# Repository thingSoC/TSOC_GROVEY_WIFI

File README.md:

# TSOC-GROVEY_WIFI

**TSOC-GROVEY_WIFI** is a Wi-Fi Embedded Module, **thingSoC Reference Design.** 

**thingSoC Reference Designs** are example thingSoC implementations that implement
various reference and testing circuits for demonstrating the use of the thingSoC libraries.
These reference designs are complete designs and can also serve as starting templates for users to customize.

**TSOC-GROVEY_WIFI** includes an ESP8266-07/12E format Wi-Fi module, in a thingSoC compatible pinout.

---------------------------------------

[  
*TSOC-GROVEY_WIFI*](https://github.com/thingSoC/thingSoC/tree/master/examples/eagle6/TSOC-GROVEY_WIFI)

* [Supported by the Arduino IDE](https://www.arduino.cc/) 
* Wi-Fi and OTA (Over the Air) Program Upgrade/Download
* thingSoC Compliant Module
* [Mikrobus Compatible Module](http://www.mikroe.com/mikrobus/) 
* ESP8266 Wi-Fi Module 802.11 b/g/n
* +19.5dBm output power in 802.11b mode
* Wi-Fi Direct (P2P), soft-AP
* Integrated TCP/IP protocol stack
* Internal Antenna and U.FL external Antenna Support

---------------------------------------

## Documentation Index <a name="documentation_index"/>

For ESP8266 Documentation (esp. toolchain info) see [NurdSpace](https://nurdspace.nl/ESP8266)

[thingSoC Organization Website](http://thingSoC.github.io)

[thingSoC FAQ - Frequently Asked Questions](http://thingsoc.github.io/support/faq.html)

---------------------------------------

[  
*thingSoC*](http://thingsoc.github.io)

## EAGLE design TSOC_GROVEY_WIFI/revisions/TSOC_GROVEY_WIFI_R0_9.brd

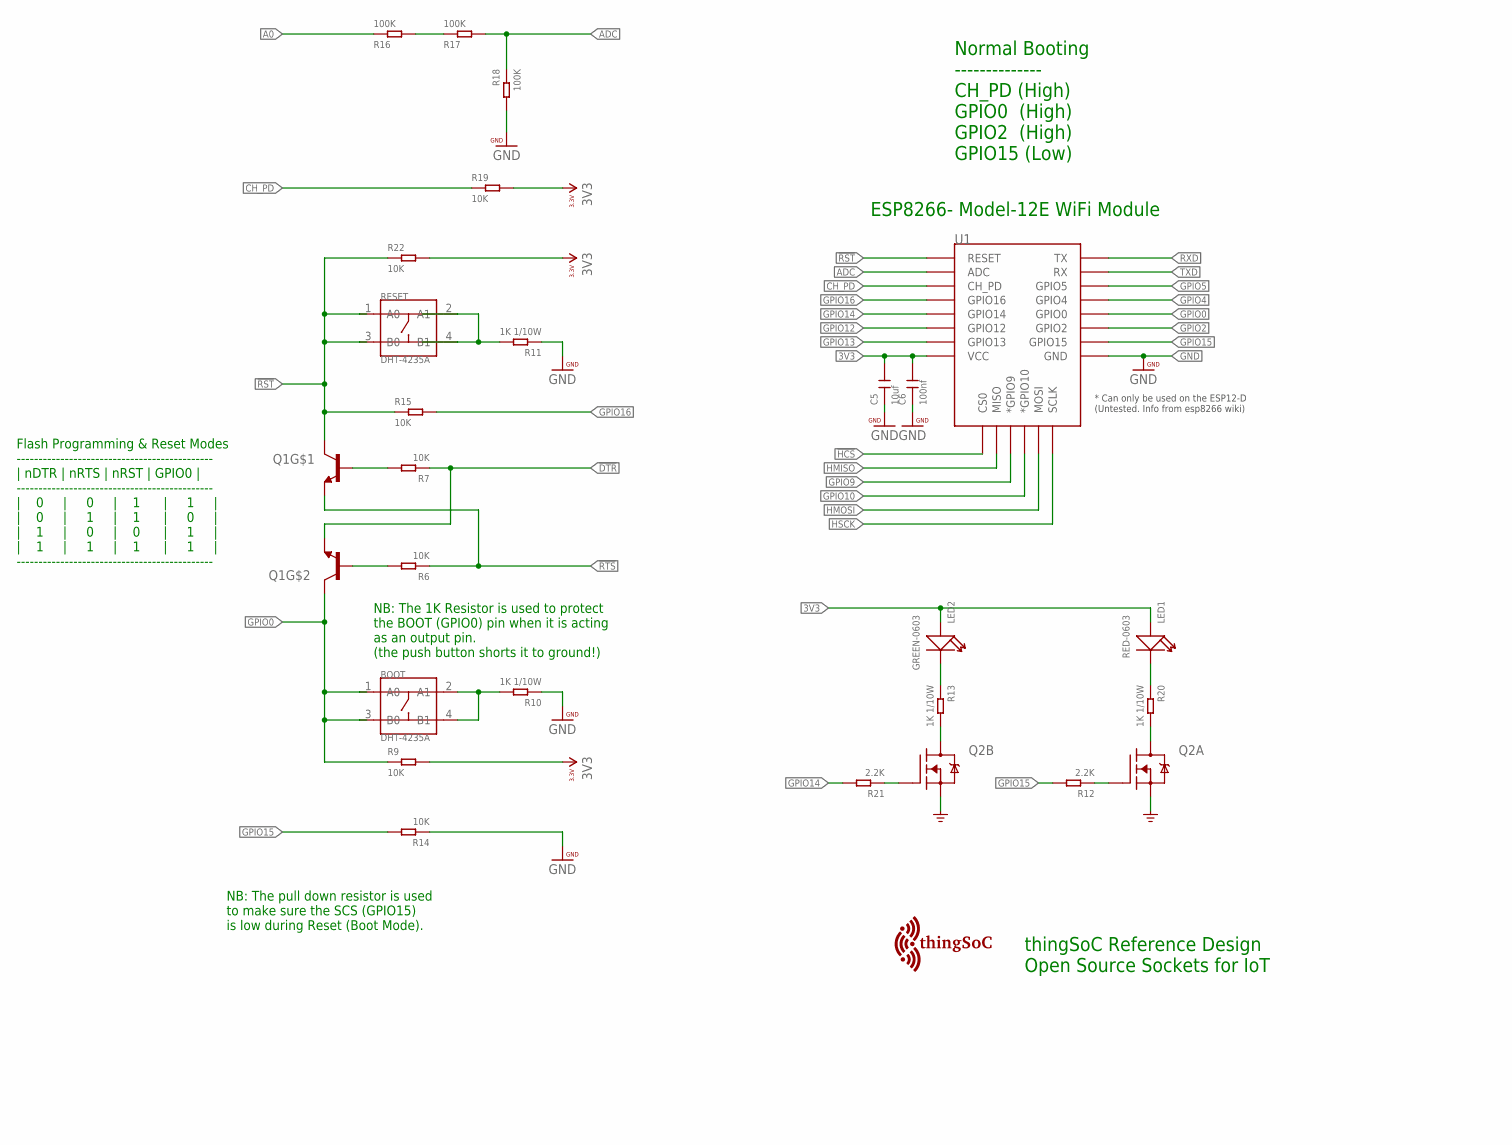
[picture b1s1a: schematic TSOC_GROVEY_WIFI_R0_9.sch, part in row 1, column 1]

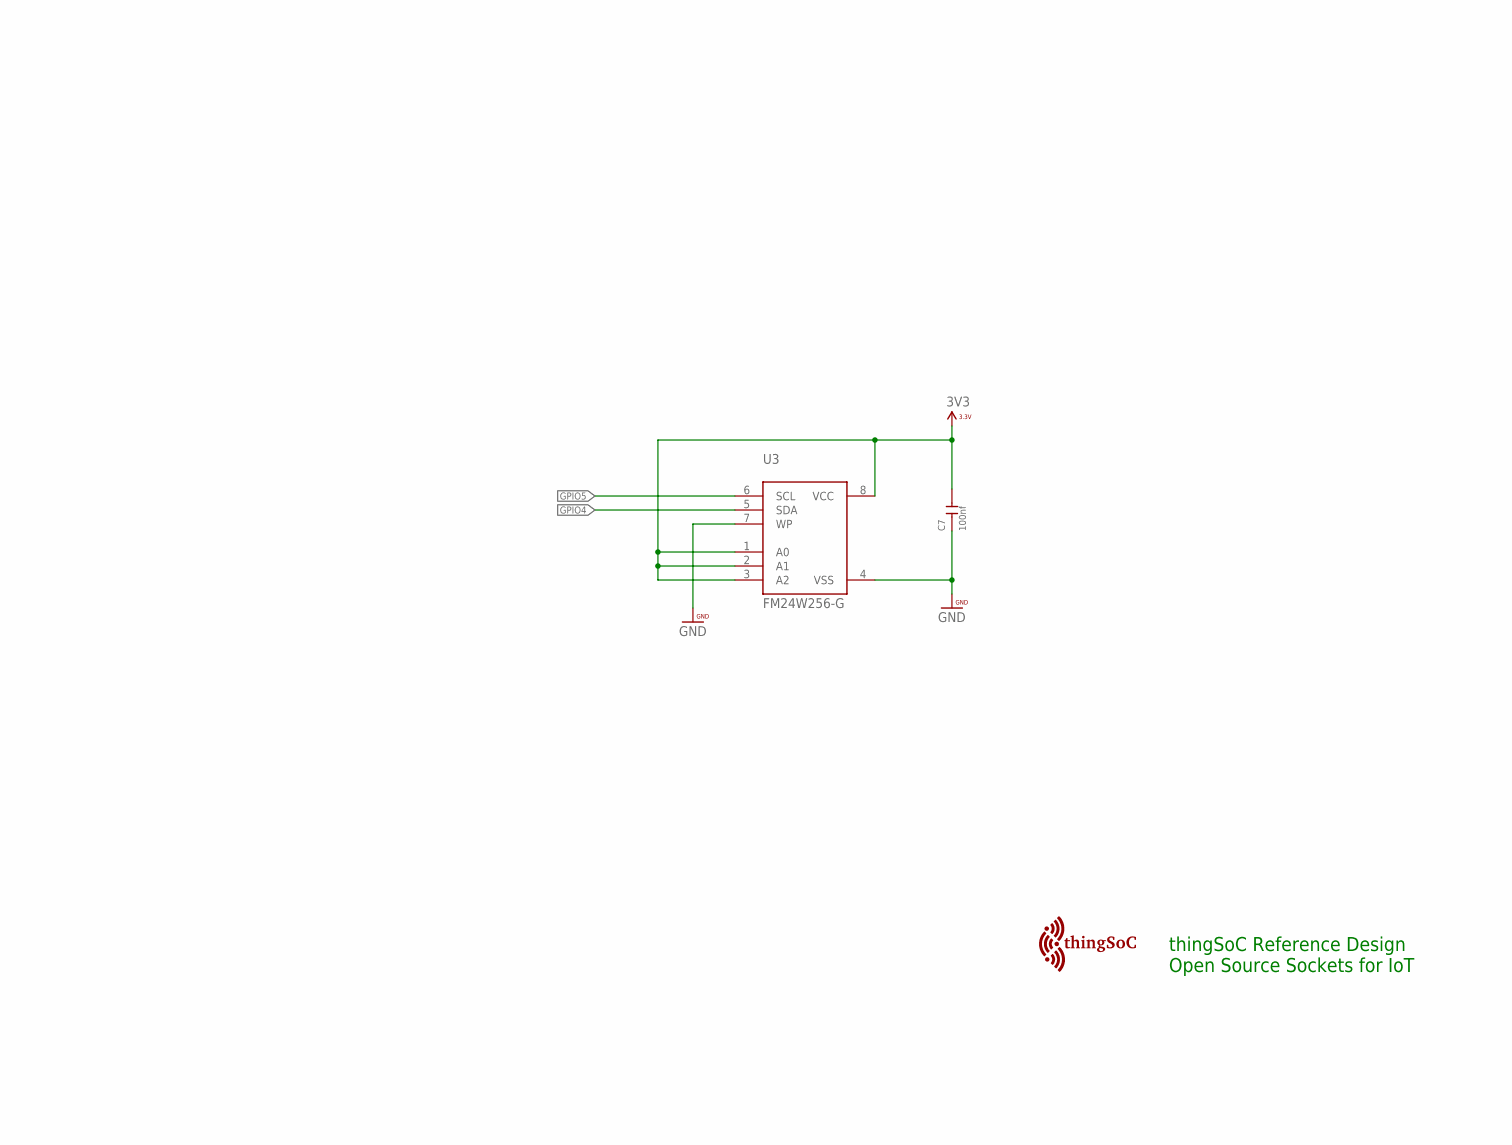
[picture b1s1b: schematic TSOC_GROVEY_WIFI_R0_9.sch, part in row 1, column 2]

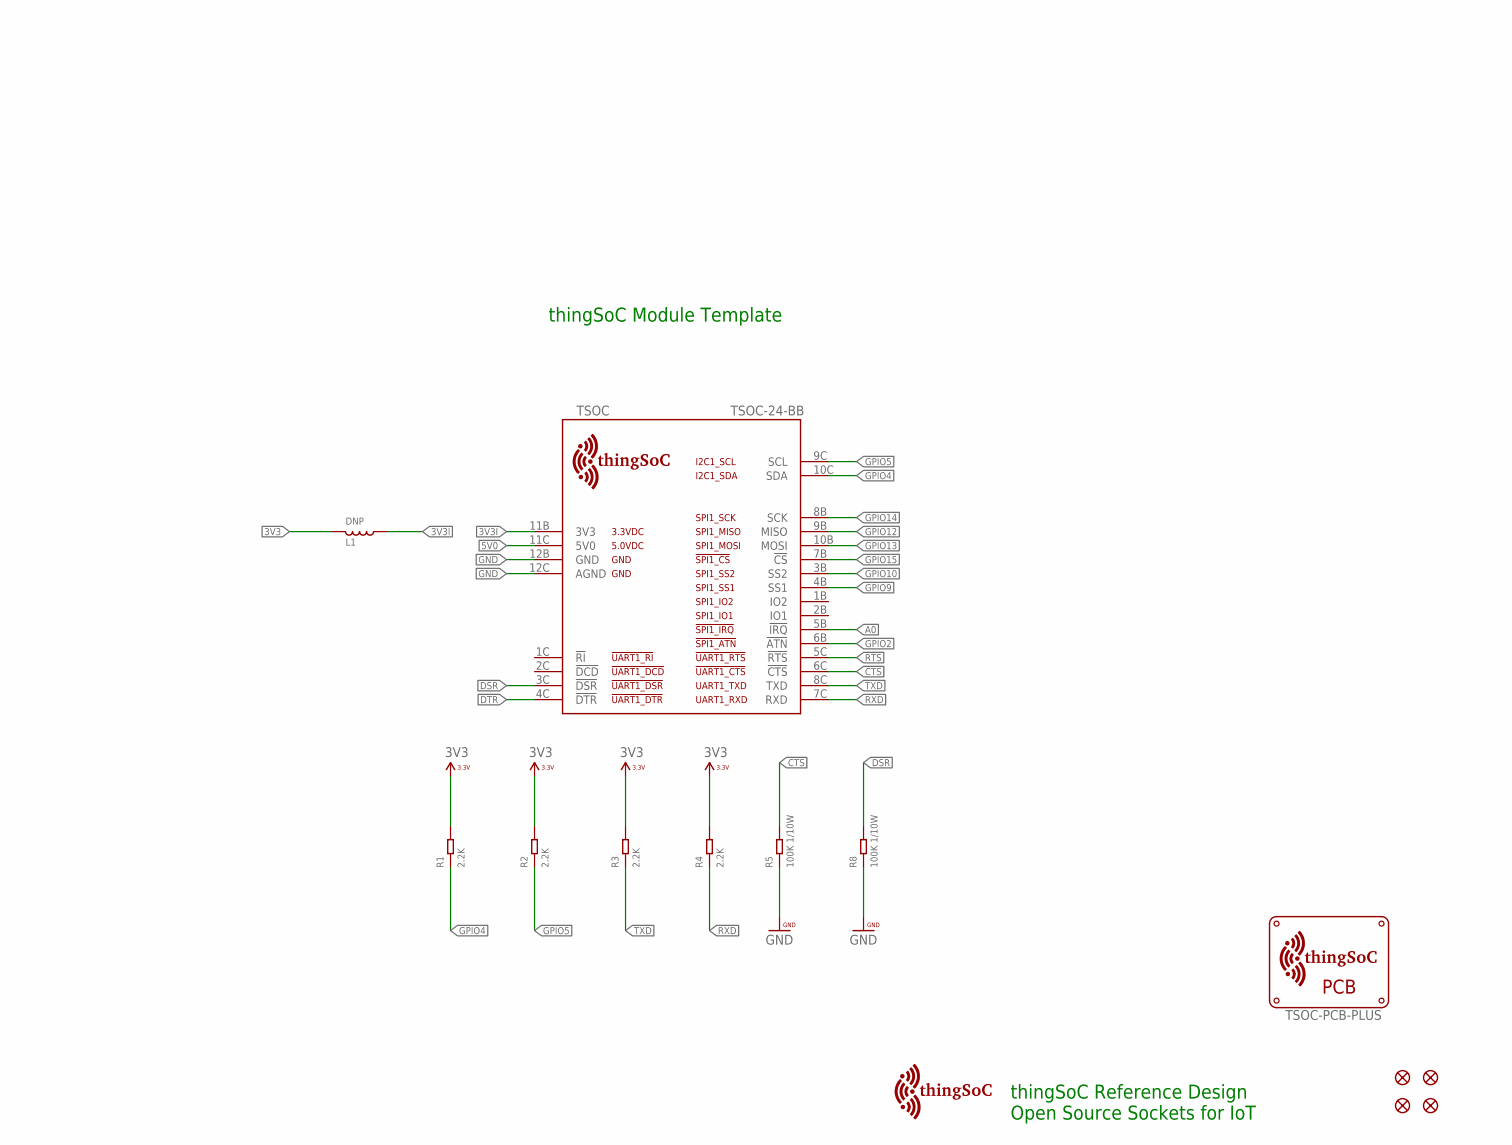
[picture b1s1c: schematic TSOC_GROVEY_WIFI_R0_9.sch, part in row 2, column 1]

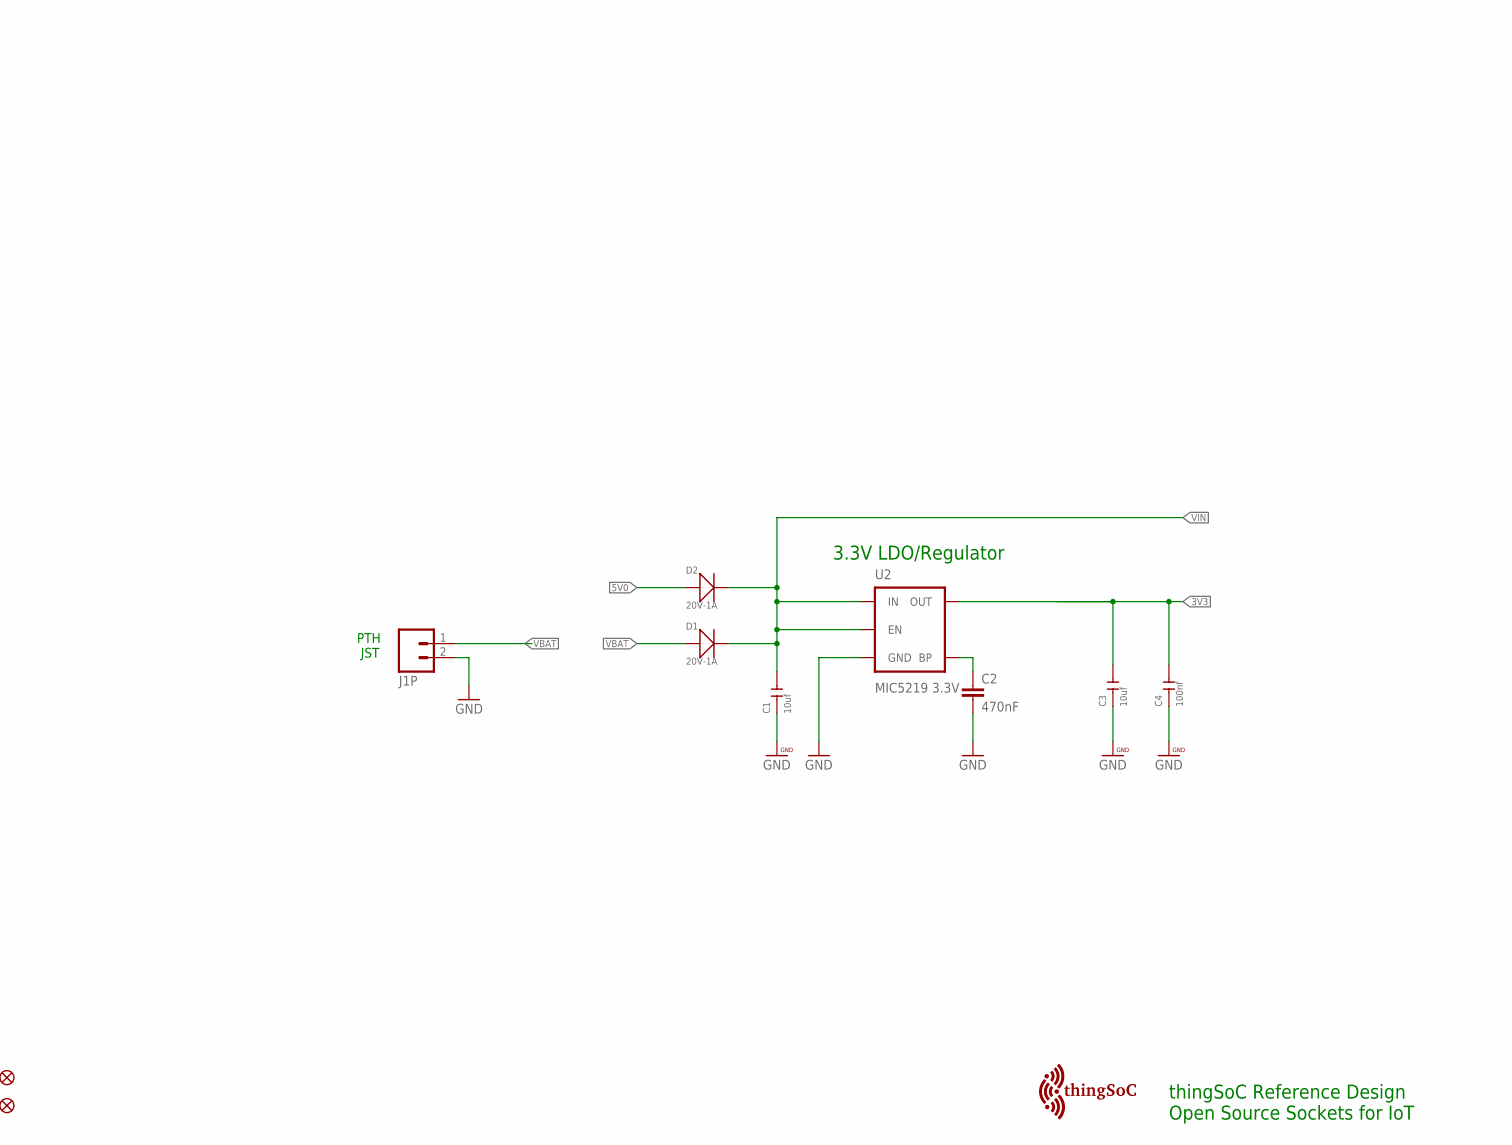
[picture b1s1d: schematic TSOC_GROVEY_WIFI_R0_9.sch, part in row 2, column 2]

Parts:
BOOT: DHT-4235A; SW4-SMD-4.2X3.2X2.5MM
C1, C3, C5: 10uf; C1206
C2: 470nF; 0402-CAP
C4, C6, C7: 100nf; C0603
D1, D2: 20V-1A; SOD-123
FID1, FID2, FID3, FID4: FIDUCIALUFIDUCIAL; MICRO-FIDUCIAL
J1P: M02-JST-2-PTH-NO_SILK; JST-2-PTH-NS
L1: DNP; L0603
LED1: RED-0603; LED-0603
LED2: GREEN-0603; LED-0603
PCB: TSOC-PCB-PLUS; TSOC-BB-BRD-PLUS-DIM
Q1: MMBT2222A; SOT363
Q2: FDG1024NZ; SOT95P280X110-6N
R1, R2, R3, R4, R12, R21: 2.2K; R0603
R5, R8: 100K 1/10W; R0603
R6, R7, R9, R14, R15, R19, R22: 10K; R0603
R10, R11, R13, R20: 1K 1/10W; R0603
R16, R17, R18: 100K; R0603
RESET: DHT-4235A; SW4-SMD-4.2X3.2X2.5MM
TSOC: TSOC-24-BB; TSOC-BB-S24
U1: ESP12ESMD; ESP12E-SMD
U2: MIC5219 3.3V; SOT23-5
U3: FM24W256-G; SO08
U$22, U$23, U$26, U$28: TSOC-LOGO-MED

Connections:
3V3: C3.2, C4.2, C5.2, C6.2, C7.2, L1.1, LED1.+, LED2.+, R1.2, R2.2, R3.2, R4.2, R9.2, R19.2, R22.2, U1.VCC, U2.5 (OUT), U3.1 (A0), U3.2 (A1), U3.3 (A2), U3.8 (VCC)
3V3I: L1.2, TSOC.11B (3V3)
5V0: D2.+, TSOC.11C (5V0)
!BOOTPD: BOOT.2 (A1), BOOT.4 (B1), R10.2
!CTS: R5.2, TSOC.6C (!CTS)
!DCDG: Q2.2 (G), R12.1
!DSR: R8.2, TSOC.3C (!DSR)
!DTR: Q1.1 (E), R7.1, TSOC.4C (!DTR)
!HCS: U1.CS0
!RST: Q1.3 (C), R15.1, R22.1, RESET.1 (A0), RESET.3 (B0), U1.RESET
!RSTPD: R11.2, RESET.2 (A1), RESET.4 (B1)
!RTS: Q1.4 (E), R6.1, TSOC.5C (!RTS)
!SCSG: Q2.5 (G), R21.1
A0: R16.1, TSOC.5B (!IRQ)
ADC: R17.2, R18.1, U1.ADC
ADC2: R16.2, R17.1
BYPASS1: C2.1, U2.4 (BP)
CH_PD: R19.1, U1.CH_PD
G0: Q2.6 (D), R20.2
G15: Q2.3 (D), R13.2
GND: C1.1, C2.2, C3.1, C4.1, C5.1, C6.1, C7.1, J1P.2, Q2.1 (S), Q2.4 (S), R5.1, R8.1, R10.1, R11.1, R14.1, R18.2, TSOC.12B (GND), TSOC.12C (AGND), U1.GND, U2.2 (GND), U3.4 (VSS), U3.7 (WP)
GPIO0: BOOT.1 (A0), BOOT.3 (B0), Q1.6 (C), R9.1, U1.GPIO0
GPIO2: TSOC.6B (!ATN), U1.GPIO2
GPIO4: R1.1, TSOC.10C (SDA), U1.GPIO4, U3.5 (SDA)
GPIO5: R2.1, TSOC.9C (SCL), U1.GPIO5, U3.6 (SCL)
GPIO9: TSOC.4B (SS1), U1.GPIO9 (*GPIO9)
GPIO10: TSOC.3B (SS2), U1.GPIO10 (*GPIO10)
GPIO12: TSOC.9B (MISO), U1.GPIO12
GPIO13: TSOC.10B (MOSI), U1.GPIO13
GPIO14: R21.2, TSOC.8B (SCK), U1.GPIO14
GPIO15: R12.2, R14.2, TSOC.7B (!CS), U1.GPIO15
GPIO16: R15.2, U1.GPIO16
HMISO: U1.MISO
HMOSI: U1.MOSI
HSCK: U1.SCLK
LED1: LED2.-, R13.1
LED2: LED1.-, R20.1
RES: Q1.5 (B), R7.2
ROS: Q1.2 (B), R6.2
RXD: R4.1, TSOC.7C (RXD), U1.TXD0 (TX)
TXD: R3.1, TSOC.8C (TXD), U1.RXD0 (RX)
VBAT: D1.+, J1P.1
VIN: C1.2, D1.-, D2.-, U2.1 (IN), U2.3 (EN)

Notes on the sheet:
thingSoC Reference Design Open Source Sockets for IoT
thingSoC Module Template
Normal Booting -------------- CH_PD (High) GPIO0 (High) GPIO2 (High) GPIO15 (Low)
ESP8266- Model-12E WiFi Module
Flash Programming & Reset Modes --------------------------------------------- | nDTR | nRTS | nRST | GPIO0 | --------------------------------------------- | 0 | 0 | 1 | 1 | | 0 | 1 | 1 | 0 | | 1 | 0 | 0 | 1 | | 1 | 1 | 1 | 1 | ---------------------------------------------
NB: The 1K Resistor is used to protect the BOOT (GPIO0) pin when it is acting as an output pin. (the push button shorts it to ground!)
NB: The pull down resistor is used to make sure the SCS (GPIO15) is low during Reset (Boot Mode).
PTH JST
3.3V LDO/Regulator

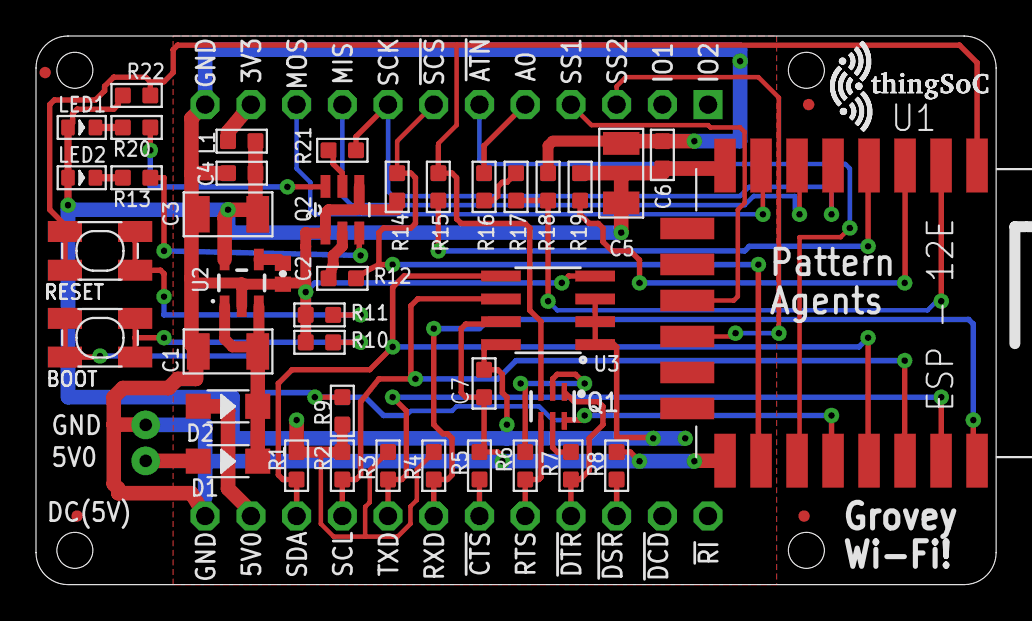
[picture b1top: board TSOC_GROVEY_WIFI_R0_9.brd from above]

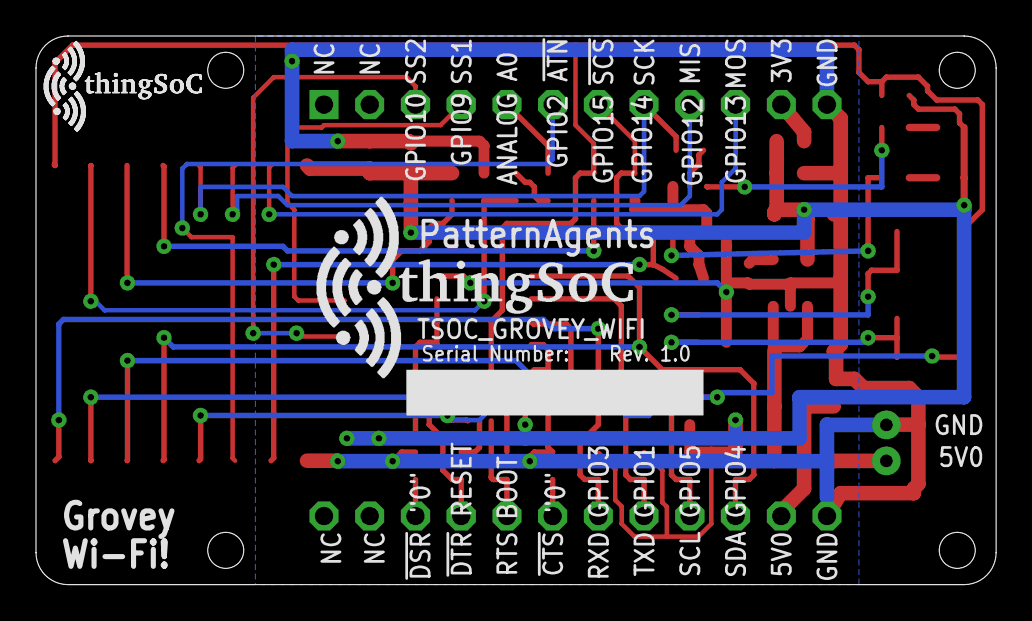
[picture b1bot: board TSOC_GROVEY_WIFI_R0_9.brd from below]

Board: 2 copper layers, 53.3 x 30.5 mm, 53 parts (3 on the bottom side), 39 nets.

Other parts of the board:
U$101: TSOC-LOGO-LRG

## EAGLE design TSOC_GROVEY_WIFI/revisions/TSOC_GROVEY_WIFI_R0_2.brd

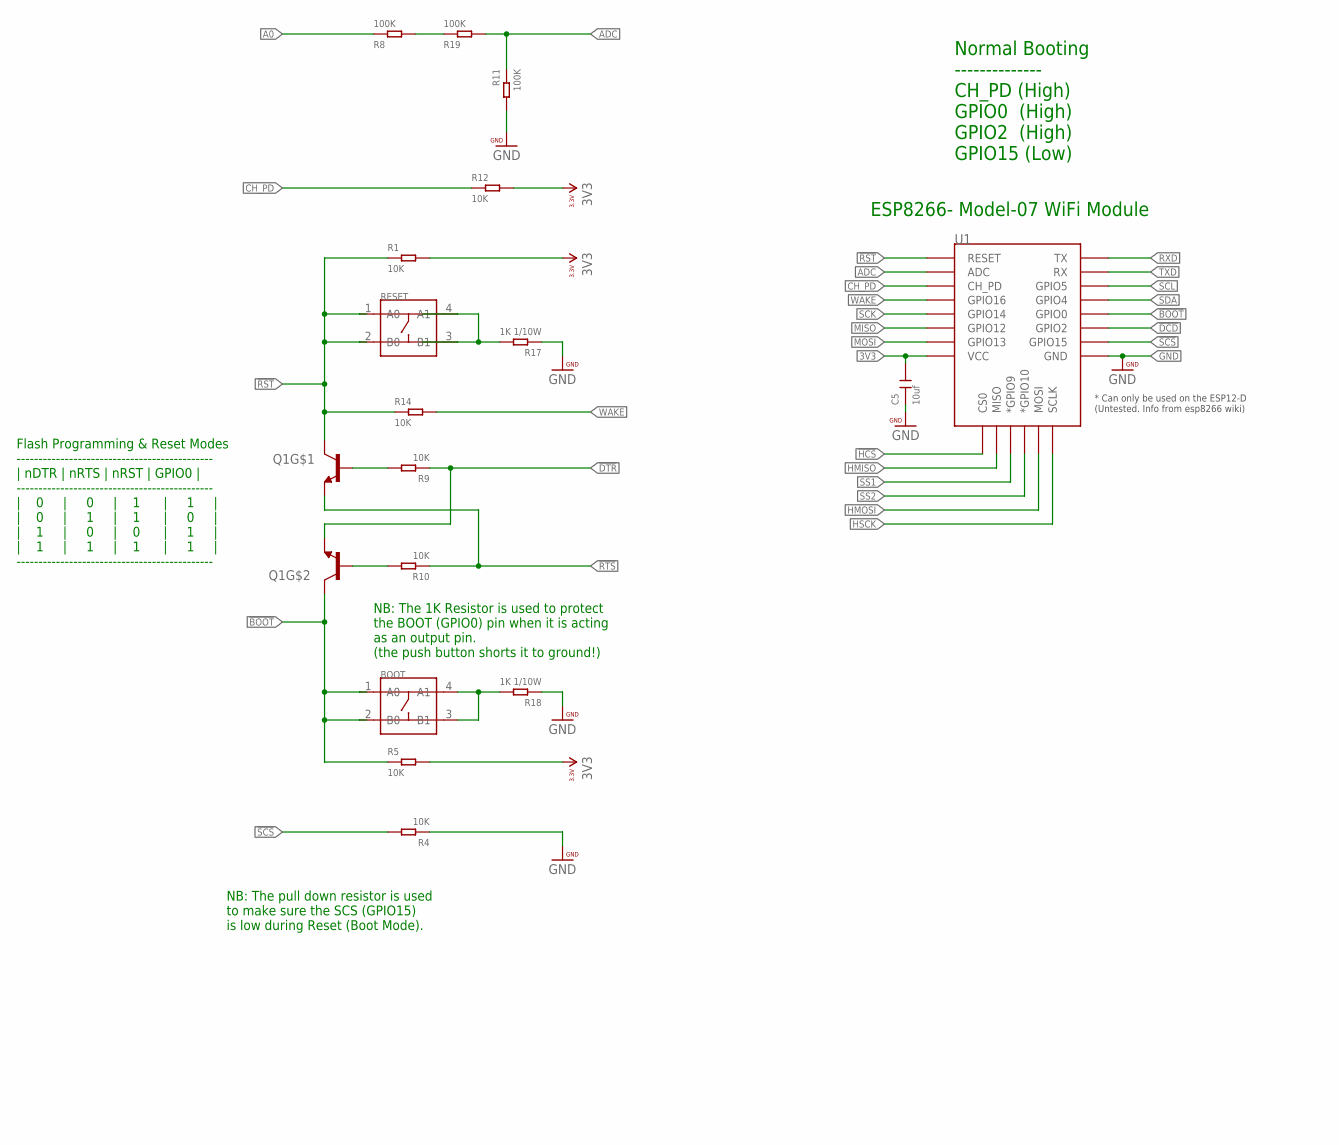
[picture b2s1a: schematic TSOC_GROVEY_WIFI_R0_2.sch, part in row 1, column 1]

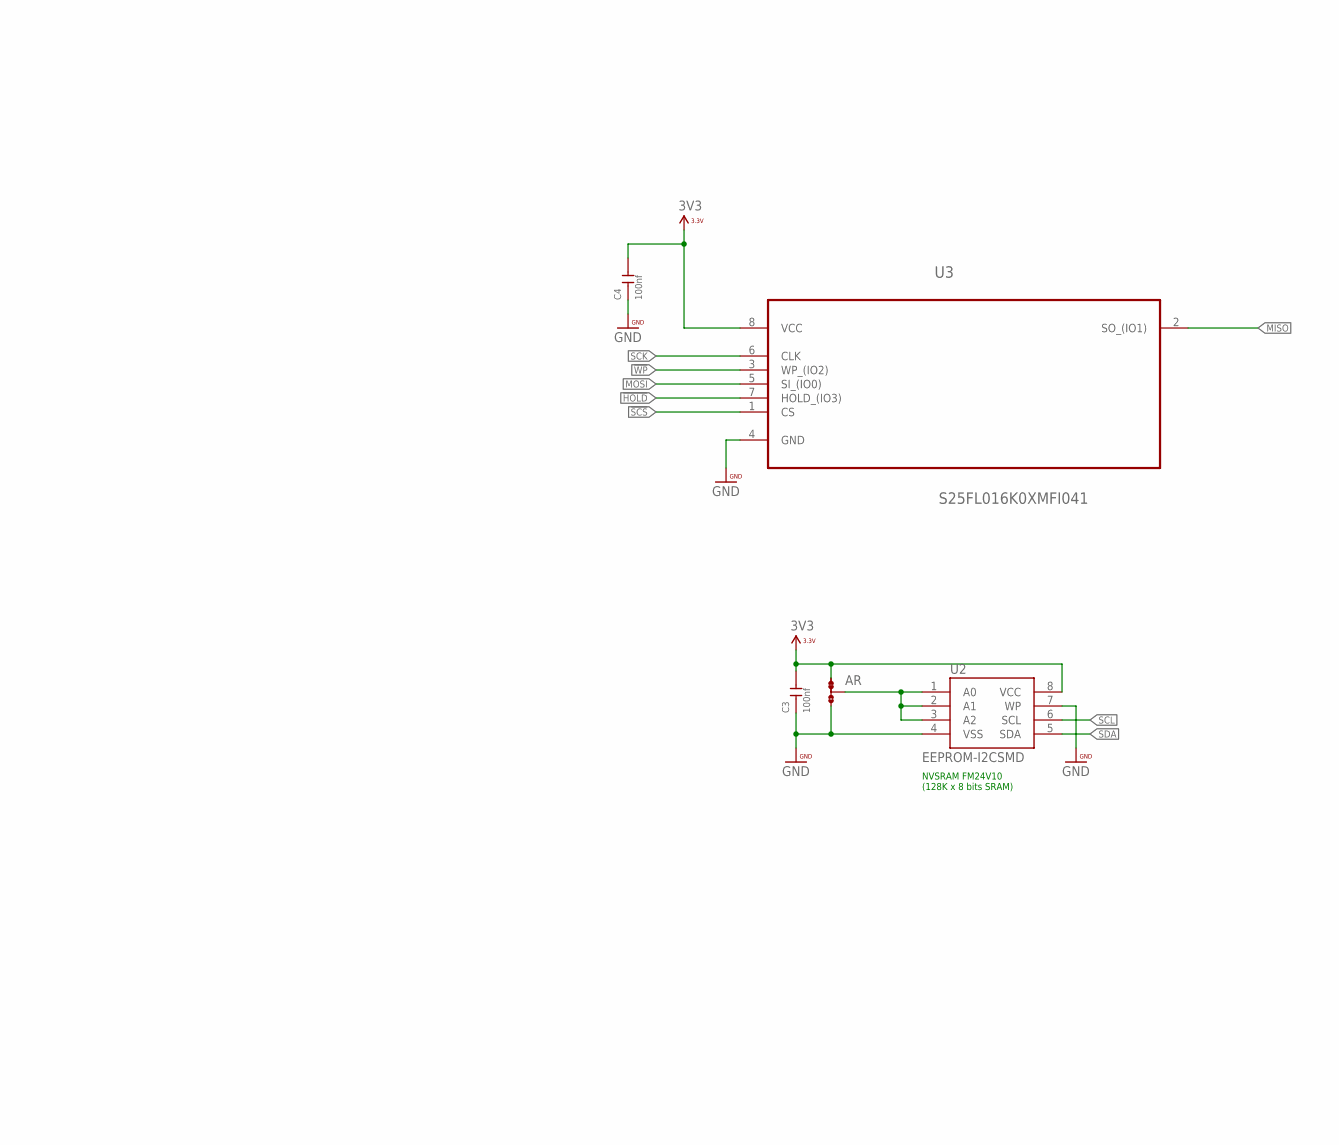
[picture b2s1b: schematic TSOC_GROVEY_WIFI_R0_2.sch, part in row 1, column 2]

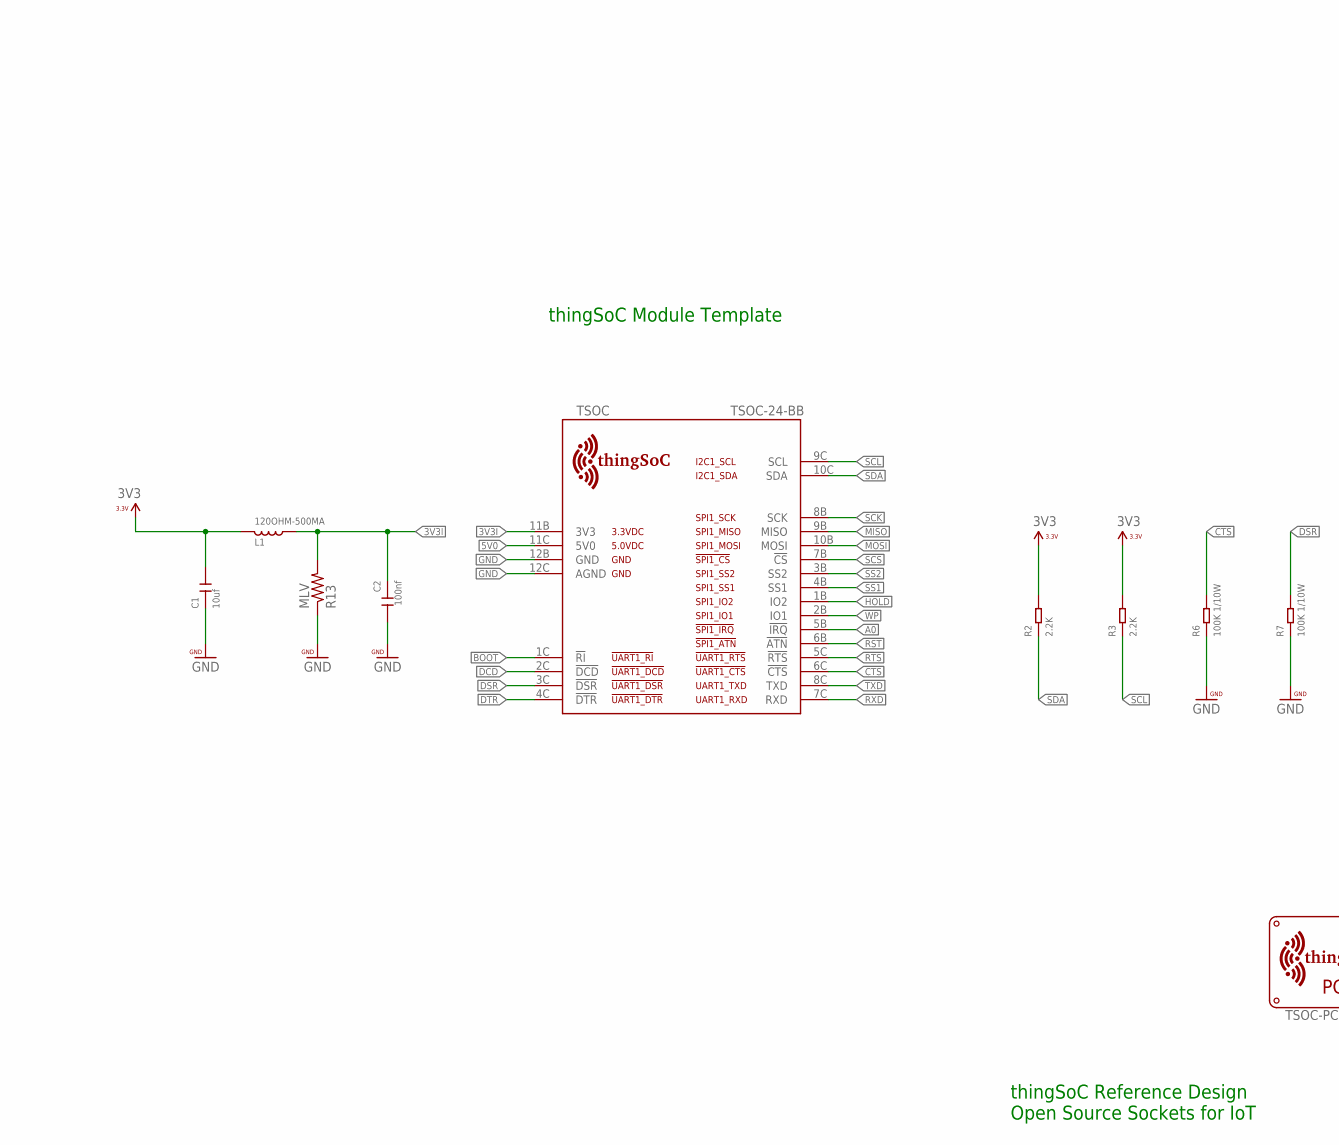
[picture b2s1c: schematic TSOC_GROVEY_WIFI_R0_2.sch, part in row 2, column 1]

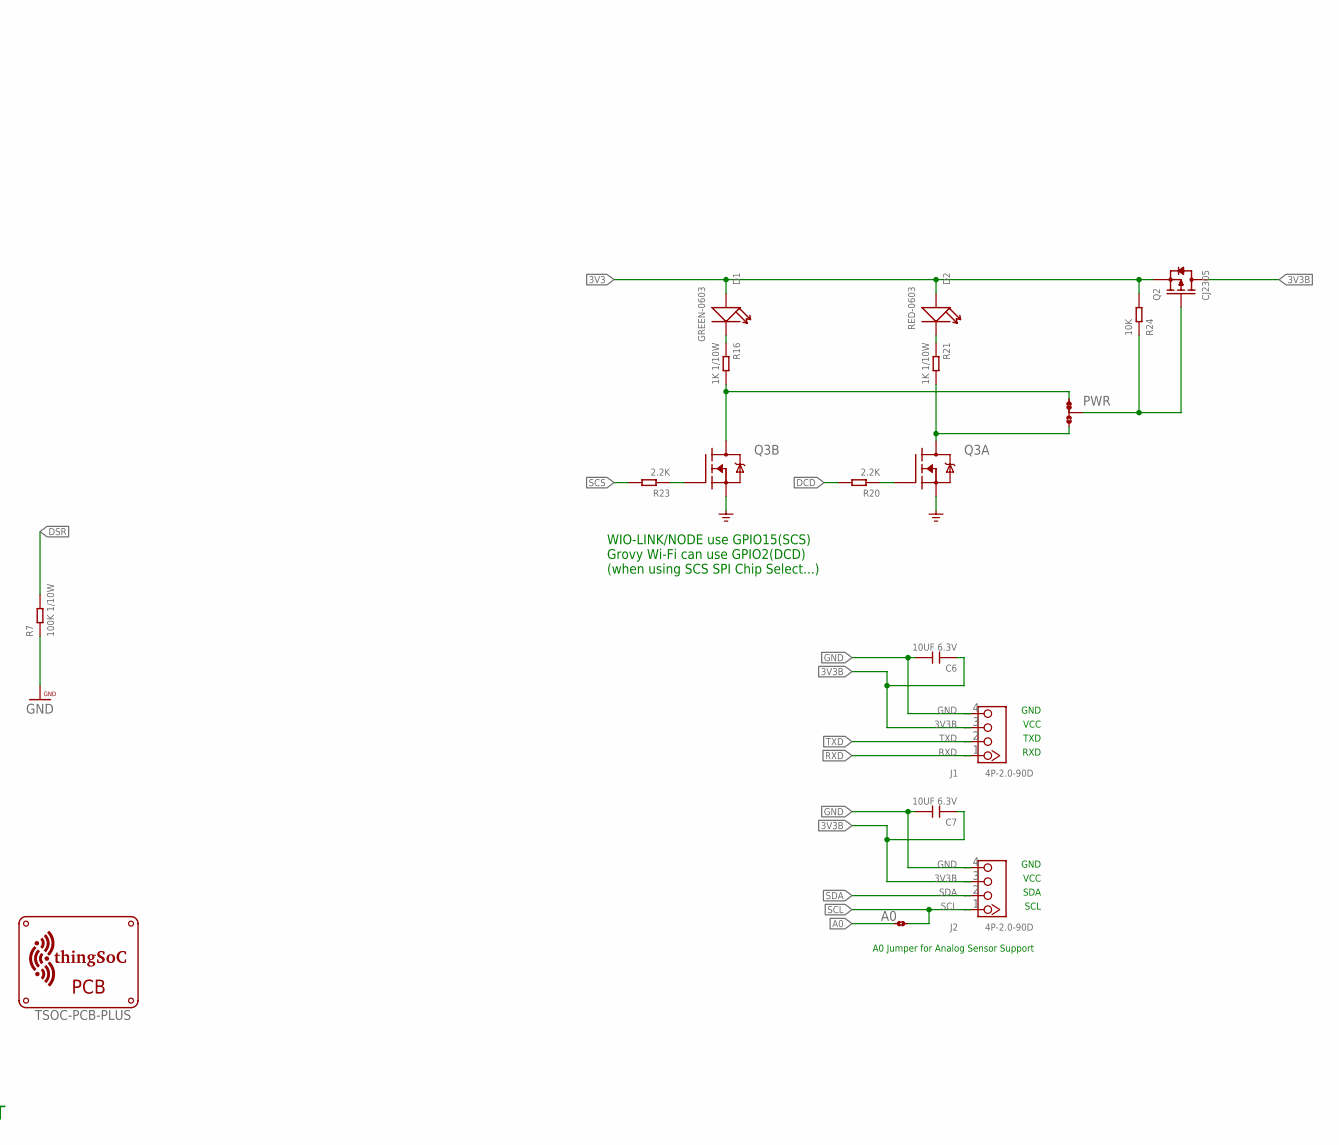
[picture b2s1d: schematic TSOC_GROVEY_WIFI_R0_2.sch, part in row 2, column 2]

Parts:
A0: JMP-2-NO
AR: JMP-3-1_2
BOOT: SMD-SWITCH-TACTILE-SPST-NO(4P-D6.0MM); SW4-SMD-6.0X6.0X5.0MM
C1, C5: 10uf; C1206
C2, C3, C4: 100nf; C0603
C6, C7: 10UF 6.3V; C0603
D1: GREEN-0603; LED-0603
D2: RED-0603; LED-0603
J1, J2: 4P-2.0-90D; HW4-2.0-90D
L1: 120OHM-500MA; L0603
PCB: TSOC-PCB-PLUS; TSOC-BB-BRD-PLUS-DIM
PWR: JMP-3-1_2
Q1: MMBT2222A; SOT363
Q2: CJ2305; SOT-23
Q3: FDG1024NZ; SOT95P280X110-6N
R1, R4, R5, R9, R10, R12, R14, R24: 10K; R0603
R2, R3, R20, R23: 2.2K; R0603
R6, R7: 100K 1/10W; R0603
R8, R11, R19: 100K; R0603
R13: MLV; 0402-RES
R16, R17, R18, R21: 1K 1/10W; R0603
RESET: SMD-SWITCH-TACTILE-SPST-NO(4P-D6.0MM); SW4-SMD-6.0X6.0X5.0MM
TSOC: TSOC-24-BB; TSOC-BB-S24
U1: ESP12ESMD; ESP12E-SMD
U2: EEPROM-I2CSMD; SO08
U3: S25FL016K0XMFI041; SOIC127P600X175-8N

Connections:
3V3: AR.1, C1.2, C3.2, C4.2, C5.2, D1.+, D2.+, L1.1, Q2.2 (S), R1.2, R2.2, R3.2, R5.2, R12.2, R24.2, U1.VCC, U2.8 (VCC), U3.8 (VCC)
3V3B: C6.1, C7.1, J1.3, J2.3, Q2.3 (D)
3V3I: C2.1, L1.2, R13.2, TSOC.11B (3V3)
5V0: TSOC.11C (5V0)
!BOOT: BOOT.1 (A0), BOOT.2 (B0), Q1.6 (C), R5.1, TSOC.1C (!RI), U1.GPIO0
!BOOTPD: BOOT.3 (B1), BOOT.4 (A1), R18.2
!CTS: R6.2, TSOC.6C (!CTS)
!DCD: R20.2, TSOC.2C (!DCD), U1.GPIO2
!DSR: R7.2, TSOC.3C (!DSR)
!DTR: Q1.1 (E), R9.1, TSOC.4C (!DTR)
!HCS: U1.CS0
!HOLD: TSOC.1B (IO2), U3.7 (HOLD_(IO3))
!RST: Q1.3 (C), R1.1, R14.1, RESET.1 (A0), RESET.2 (B0), TSOC.6B (!ATN), U1.RESET
!RSTPD: R17.2, RESET.3 (B1), RESET.4 (A1)
!RTS: Q1.4 (E), R10.1, TSOC.5C (!RTS)
!SCS: R4.2, R23.2, TSOC.7B (!CS), U1.GPIO15, U3.1 (CS)
!WP: TSOC.2B (IO1), U3.3 (WP_(IO2))
A0: A0.2, R8.1, TSOC.5B (!IRQ)
ADC: R11.1, R19.2, U1.ADC
ADC2: R8.2, R19.1
CH_PD: R12.1, U1.CH_PD
G0: PWR.3, Q3.6 (D), R21.2
G15: PWR.1, Q3.3 (D), R16.2
GND: AR.3, C1.1, C2.2, C3.1, C4.1, C5.1, C6.2, C7.2, J1.4, J2.4, Q3.1 (S), Q3.4 (S), R4.1, R6.1, R7.1, R11.2, R13.1, R17.1, R18.1, TSOC.12B (GND), TSOC.12C (AGND), U1.GND, U2.4 (VSS), U2.7 (WP), U3.4 (GND)
GROVEPWR: PWR.2, Q2.1 (G), R24.1
HMISO: U1.MISO
HMOSI: U1.MOSI
HSCK: U1.SCLK
LED1: D1.-, R16.1
LED2: D2.-, R21.1
MISO: TSOC.9B (MISO), U1.GPIO12, U3.2 (SO_(IO1))
MOSI: TSOC.10B (MOSI), U1.GPIO13, U3.5 (SI_(IO0))
unnamed: AR.2, U2.1 (A0), U2.2 (A1), U2.3 (A2)
unnamed: Q1.5 (B), R9.2
unnamed: Q3.2 (G), R20.1
unnamed: Q3.5 (G), R23.1
unnamed: Q1.2 (B), R10.2
RXD: J1.1, TSOC.7C (RXD), U1.TXD0 (TX)
SCK: TSOC.8B (SCK), U1.GPIO14, U3.6 (CLK)
SCL: A0.1, J2.1, R3.1, TSOC.9C (SCL), U1.GPIO5, U2.6 (SCL)
SDA: J2.2, R2.1, TSOC.10C (SDA), U1.GPIO4, U2.5 (SDA)
SS1: TSOC.4B (SS1), U1.GPIO9 (*GPIO9)
SS2: TSOC.3B (SS2), U1.GPIO10 (*GPIO10)
TXD: J1.2, TSOC.8C (TXD), U1.RXD0 (RX)
WAKE: R14.2, U1.GPIO16

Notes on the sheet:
thingSoC Reference Design Open Source Sockets for IoT
thingSoC Module Template
Normal Booting -------------- CH_PD (High) GPIO0 (High) GPIO2 (High) GPIO15 (Low)
ESP8266- Model-07 WiFi Module
Flash Programming & Reset Modes --------------------------------------------- | nDTR | nRTS | nRST | GPIO0 | --------------------------------------------- | 0 | 0 | 1 | 1 | | 0 | 1 | 1 | 0 | | 1 | 0 | 0 | 1 | | 1 | 1 | 1 | 1 | ---------------------------------------------
NVSRAM FM24V10 (128K x 8 bits SRAM)
GND
VCC
TXD
RXD
SDA
SCL
A0 Jumper for Analog Sensor Support
WIO-LINK/NODE use GPIO15(SCS) Grovy Wi-Fi can use GPIO2(DCD) (when using SCS SPI Chip Select...)
NB: The 1K Resistor is used to protect the BOOT (GPIO0) pin when it is acting as an output pin. (the push button shorts it to ground!)
NB: The pull down resistor is used to make sure the SCS (GPIO15) is low during Reset (Boot Mode).

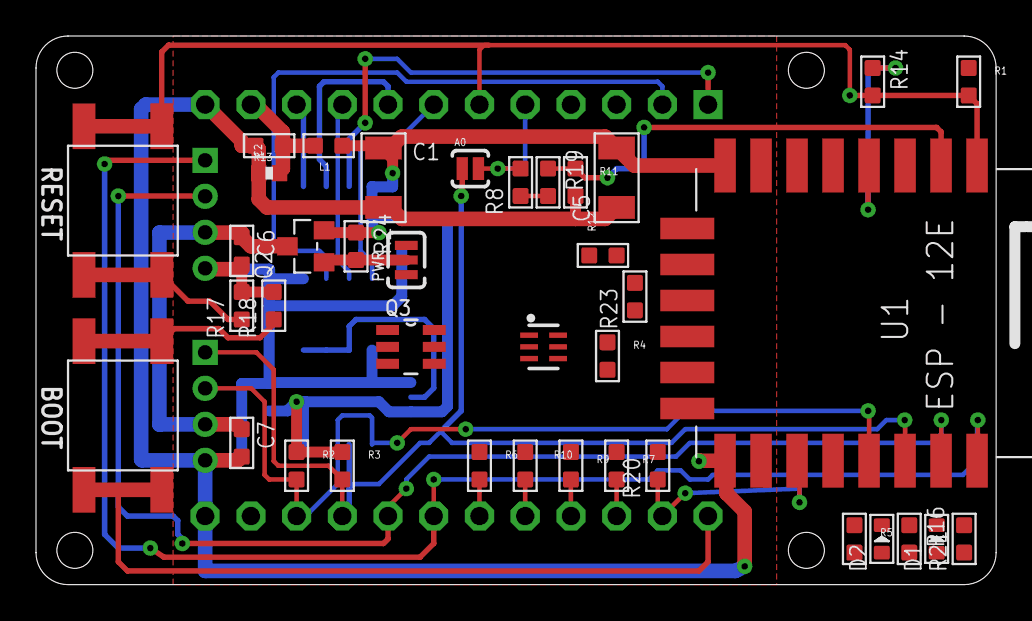
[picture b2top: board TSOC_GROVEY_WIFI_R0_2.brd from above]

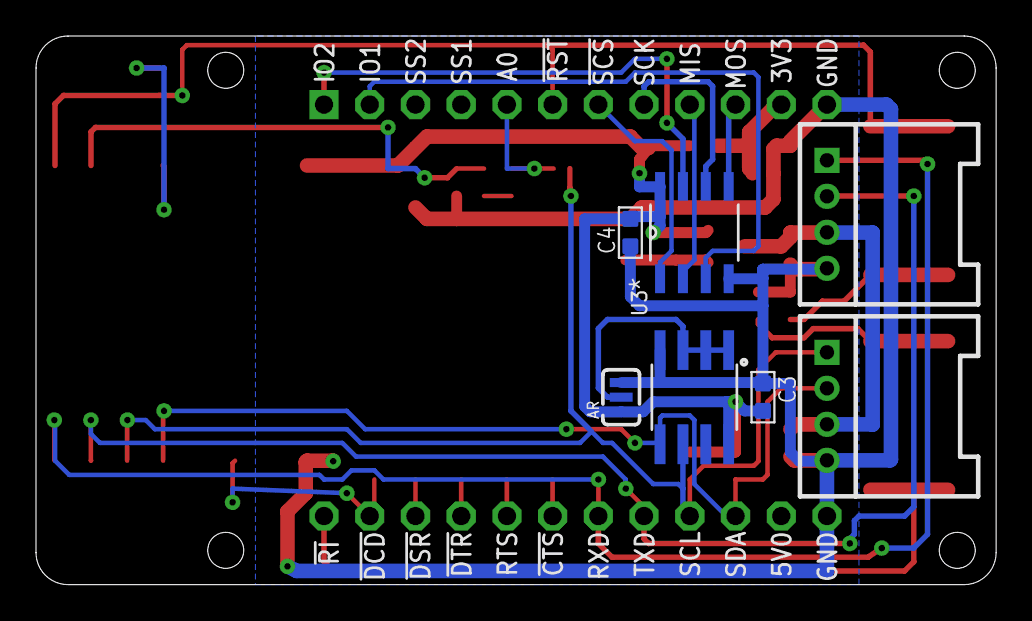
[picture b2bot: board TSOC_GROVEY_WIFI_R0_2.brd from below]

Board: 2 copper layers, 53.3 x 30.5 mm, 47 parts (7 on the bottom side), 40 nets.

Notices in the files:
parts and their libraries:
PatternAgents-ProtoPads: License : http://creativecommons.org/licenses/by-sa/4.0
(Creative Commons 4.0)
SparkFun-DiscreteSemi: Licensing: Creative Commons ShareAlike 4.0 International - https://creativecommons.org/licenses/by-sa/4.0
PatternAgents-Fairchild: (Creative Commons 3.0)
